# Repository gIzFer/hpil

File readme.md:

# HP-IL bridge/translator to USB/Serial

## What does it do
So what does this do? The device simply takes what it receives from the HP-IL side and sends it over serial. Same in the other direction. sends 2 bytes, the `command` and the `data` terminated with a `'\n'` (ascii 10) character

## Why
I had a 3468A and wanted to control it from my computer and make the electronics circuit simple an easy and of parts everyone could have at hand. Difficulty was relayed onto the firmware, but even so was kept simple without implementing the state machines of the protocol.

## Materials needed
- Atmega328p
- 2 NPN and 4 PNP transistors. 2 PNP handle the input and the other 2 and 2 are for a push pull arrangement to send data. I sprinkled on them some diodes to speed them up.
- Ethernet transformer. Fastest pulses are around 1µs and an ethernet transformer seems to be able to handle that quite well. You can find them in every device having a rj45 port, old computers, routers, switches, etc.

[client docs](./client/readme.md)

## Added made up codes

### 1XX

They are for extra messages you can send to the device, like asking it to just send the message it just received

#### 1XX List of codes
- 101: send back the last message received
- 102: get calibration data of the HP3468 dmm
- 103: get firmware version
- 104: set calibration value of the HP3468 dmm. Has 5 parameters: first one is the range setting to set. Since there are 12 ranges and two values per range the even values are offsets and odd values are gains. i.e.: `104 6 0 0 0 0` set the offset of the fourth range to 0.i.e.: `104 1 0 0 0 0` set the gain of the first range to 0.
- 105: print processed calibration values of the HP3468 dmm
- 106: print a quick read of the HP3468 dmm

### 2XX

They are for extra messages you can receive from the device  like errors

#### 2XX List of codes
- 201: received message buffer overflowed, answers with 201 and the last byte it received
- 202: in command 104, trying to set a cal value the value was more than 23; there are only 12 ranges with 2 values per range (offset and gain), 0 to 23.

# todo:
- read pins instead of delays (NOPs) when talking to be able to read answer at the same time im writing
- add images to readme
- add "console mode" so no need for the python client, to be able to directly send the commands to it
- send and write calibration data

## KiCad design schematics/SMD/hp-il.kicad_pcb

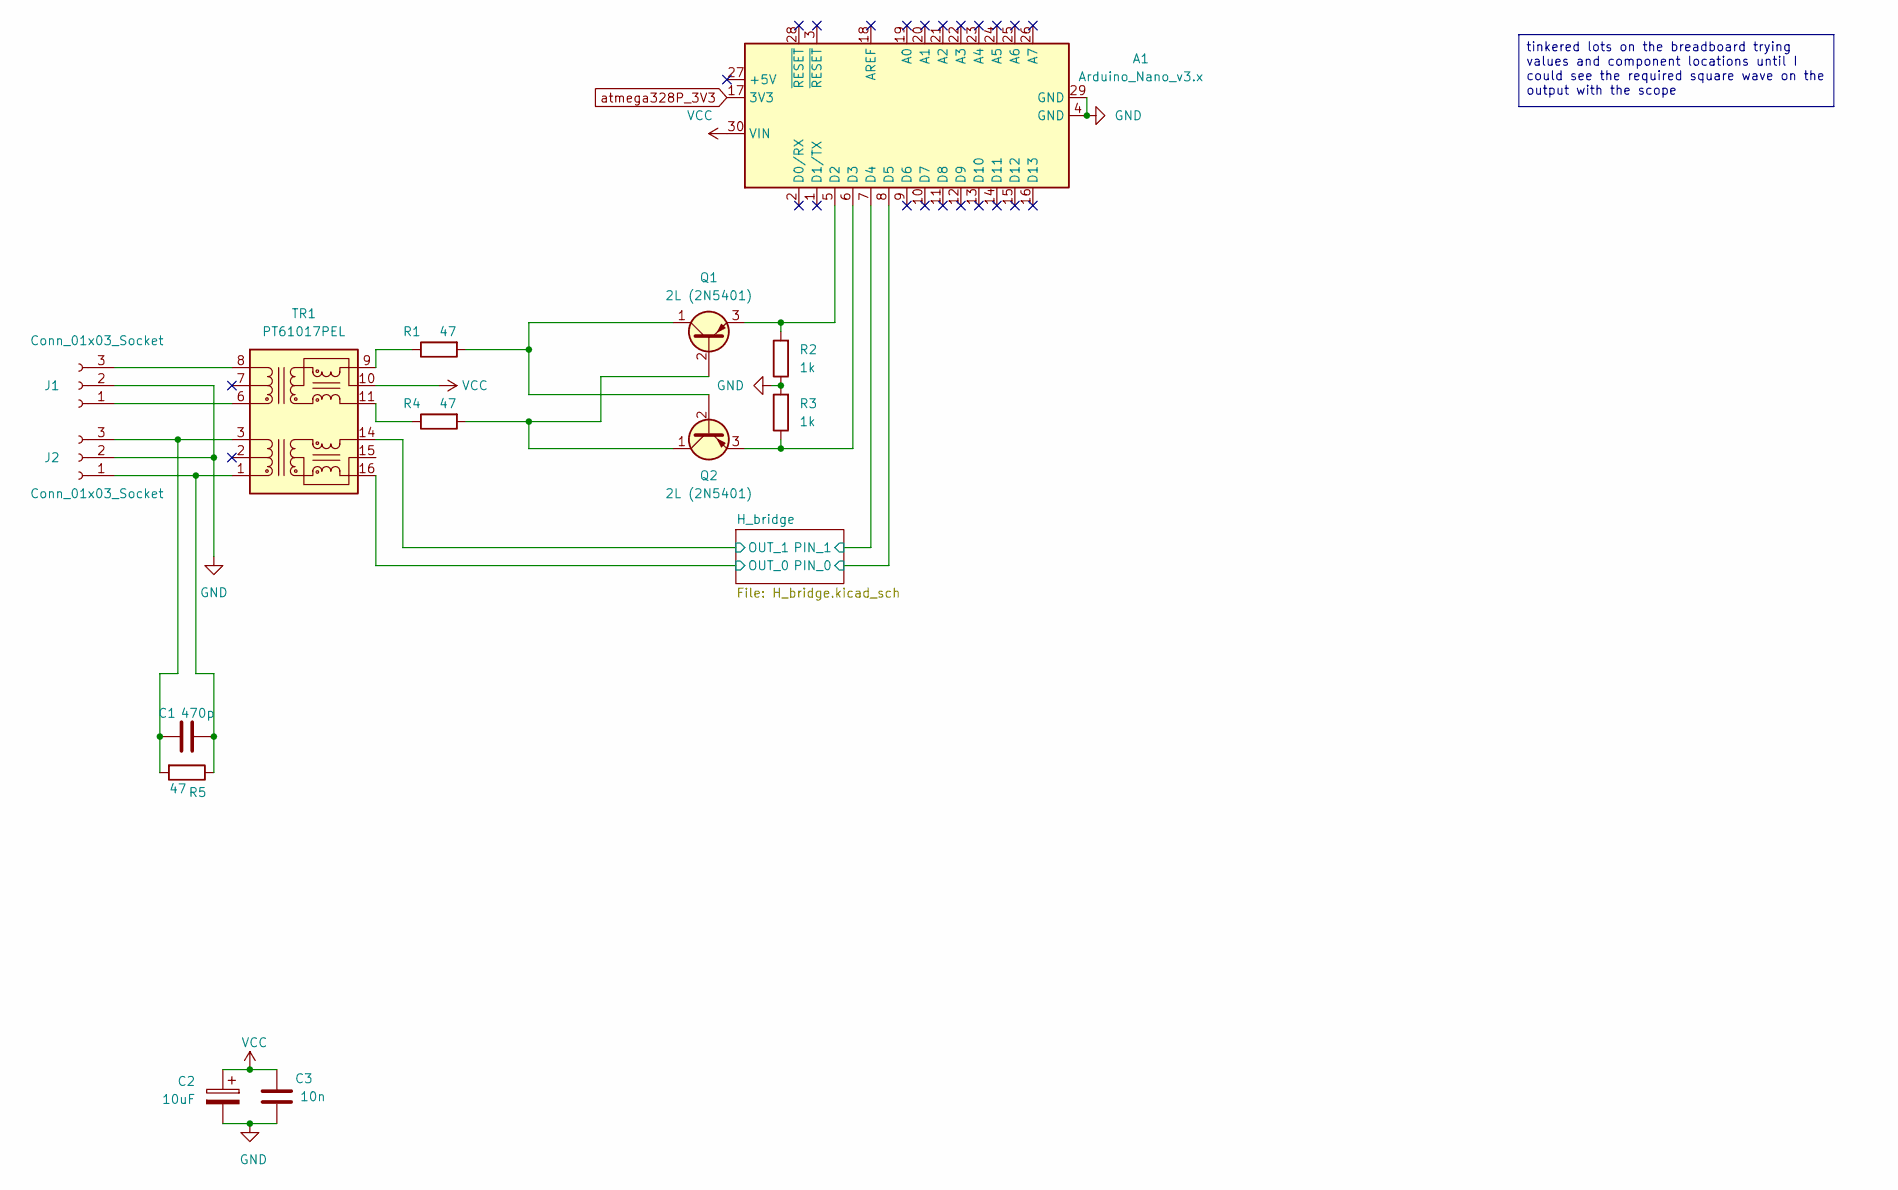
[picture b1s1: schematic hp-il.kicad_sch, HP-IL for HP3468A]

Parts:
A1: Arduino_Nano_v3.x; Arduino_Nano
C1: 470p; C_0603_1608Metric_Pad1.08x0.95mm_HandSolder
C2: 10uF; CP_Radial_D4.0mm_P2.00mm
C3: 10n; C_0603_1608Metric_Pad1.08x0.95mm_HandSolder
J1, J2: Conn_01x03_Socket; PinHeader_1x03_P2.54mm_Vertical
Q1, Q2: 2L (2N5401); SOT-23_Handsoldering_(5401_2L)
R1, R4, R5: 47; R_0603_1608Metric_Pad0.98x0.95mm_HandSolder
R2, R3: 1k; R_0603_1608Metric_Pad0.98x0.95mm_HandSolder
TR1: PT61017PEL; Transformer_Ethernet_Bourns_PT61017PEL

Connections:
/H_bridge/OUT_0: TR1.16 (TX+); also elsewhere on the board
/H_bridge/OUT_1: TR1.14 (TX-); also elsewhere on the board
/H_bridge/PIN_0: A1.8 (D5); also elsewhere on the board
/H_bridge/PIN_1: A1.7 (D4); also elsewhere on the board
GND: A1.4 (GND), A1.29 (GND), C2.2, C3.2, J1.2, J2.2, R2.1, R3.2; also elsewhere on the board
unnamed: A1.5 (D2), Q1.3 (E), R2.2
unnamed: A1.6 (D3), Q2.3 (E), R3.1
unnamed: J1.1, TR1.6 (RD+)
unnamed: J1.3, TR1.8 (RD-)
unnamed: C1.2, J2.1, R5.1, TR1.1 (TD+)
unnamed: C1.1, J2.3, R5.2, TR1.3 (TD-)
unnamed: Q1.2 (B), Q2.1 (C), R4.2
unnamed: Q1.1 (C), Q2.2 (B), R1.2
unnamed: R4.1, TR1.11 (RX+)
unnamed: R1.1, TR1.9 (RX-)
VCC: A1.30 (VIN), C2.1, C3.1, TR1.10 (C_RX)
atmega328P_3V3: A1.17 (3V3); also elsewhere on the board

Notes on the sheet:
tinkered lots on the breadboard trying values and component locations until I could see the required square wave on the output with the scope

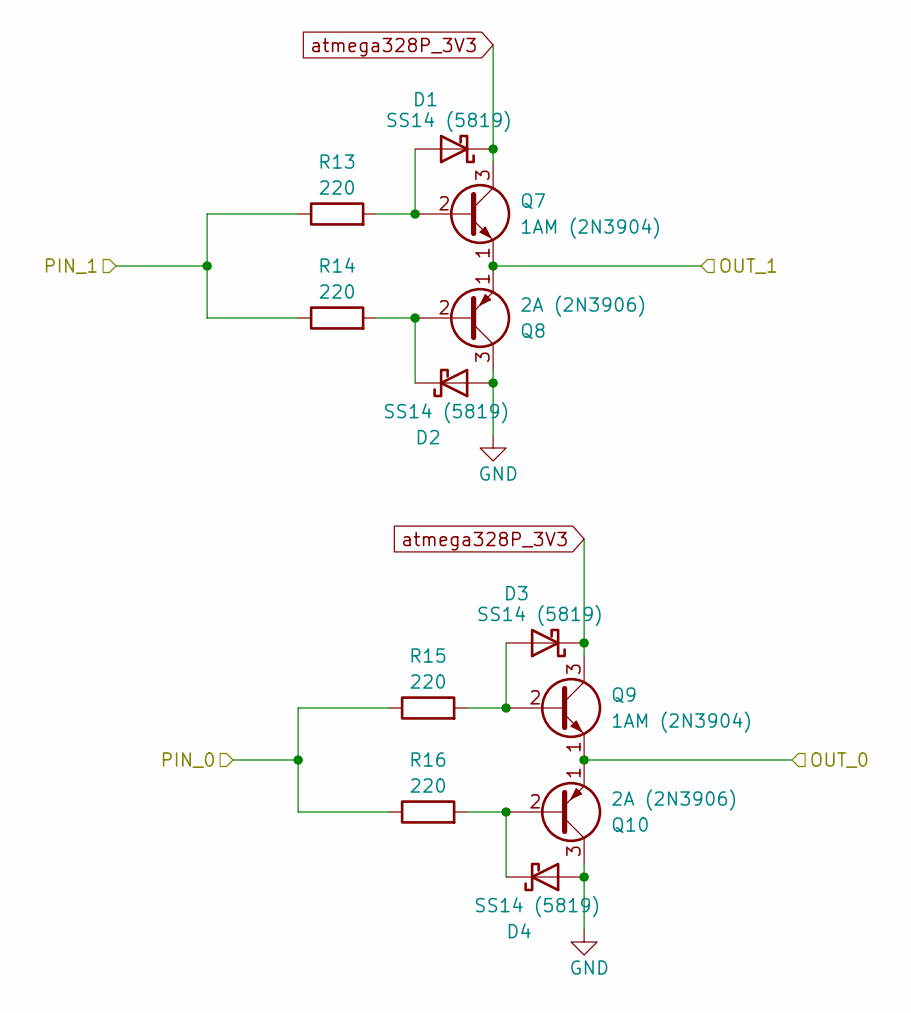
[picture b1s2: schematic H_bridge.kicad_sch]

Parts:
D1, D2, D3, D4: SS14 (5819); D_SMA_Handsoldering
Q7, Q9: 1AM (2N3904); SOT-23_Handsoldering_(3904_1AM)(3906_2A)
Q8, Q10: 2A (2N3906); SOT-23_Handsoldering_(3904_1AM)(3906_2A)
R13, R14, R15, R16: 220; R_0603_1608Metric_Pad0.98x0.95mm_HandSolder

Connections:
/H_bridge/OUT_0: Q9.1 (E), Q10.1 (E); also elsewhere on the board
/H_bridge/OUT_1: Q7.1 (E), Q8.1 (E); also elsewhere on the board
/H_bridge/PIN_0: R15.1, R16.1; also elsewhere on the board
/H_bridge/PIN_1: R13.1, R14.1; also elsewhere on the board
GND: D2.2 (A), D4.2 (A), Q8.3 (C), Q10.3 (C); also elsewhere on the board
unnamed: D1.2 (A), Q7.2 (B), R13.2
unnamed: D2.1 (K), Q8.2 (B), R14.2
unnamed: D3.2 (A), Q9.2 (B), R15.2
unnamed: D4.1 (K), Q10.2 (B), R16.2
atmega328P_3V3: D1.1 (K), D3.1 (K), Q7.3 (C), Q9.3 (C); also elsewhere on the board

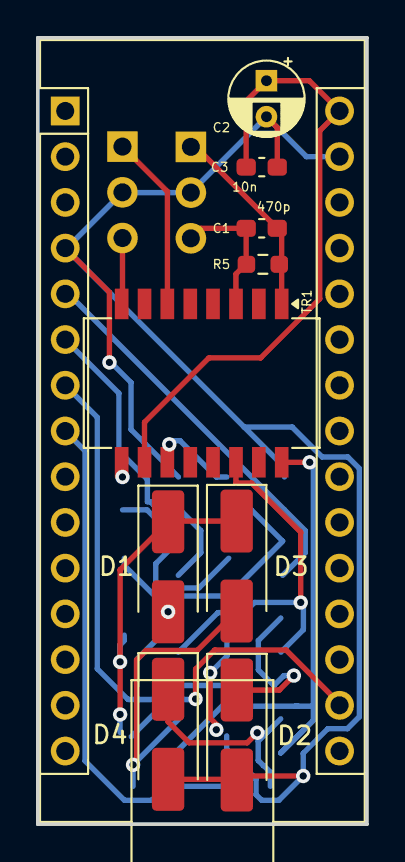
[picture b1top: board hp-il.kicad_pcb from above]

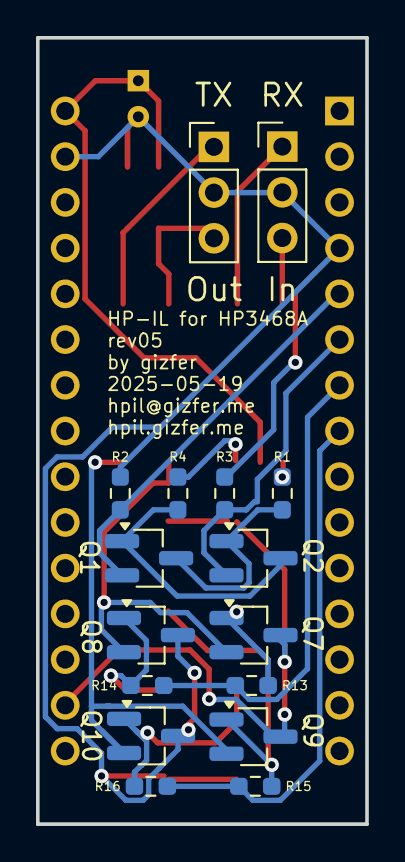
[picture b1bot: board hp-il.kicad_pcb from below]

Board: 2 copper layers, 18.3 x 43.7 mm, 26 parts (16 on the bottom side), 21 nets.

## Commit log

2023-11-02 optimized, it can now keep up
2023-11-02 split into files for organization
2023-11-08 can now send pulses through
2024-02-06 Can receive and talk
2024-02-07 kinda rebase
2024-02-08 kinda rebase 2
2024-02-08 it works
2024-02-08 it works 2
2024-03-07 added hpil class for control
2024-03-09 workssss
2024-03-09 added messages
2024-03-09 working and cleaned
2024-03-09 optimized and cleaned
2024-12-01 works :DDD
2024-12-02 minor rework, added comments
2024-12-02 added schematic and client
2024-12-02 renamed schematic folder and cleaned files
2024-12-02 added .gitignore to schematics
2024-12-02 added and organized .gitignores
2024-12-02 firmware code cleanup
2024-12-02 worked on docs
2024-12-02 added to the todo list
2024-12-02 Create LICENSE
    added a license
2025-06-15 bugfixes on the signal decoding
2025-06-16 added retry system with talk and rawTalk
2025-06-16 added getCal method
2025-06-16 added "console mode" to the todo list
2025-06-16 added GetCal "docs"
2025-06-16 created compact SMD version, kept THT one
2025-06-16 removed upload.sh, using make
2025-06-20 added get cal data code 102
2025-06-20 added boot str to detect when ready
2025-06-20 added firmware version
2025-06-20 updated client with new features
2025-06-28 added code to decode and encode gain value
2025-06-28 specified detail on custom code
2025-06-28 added calculation of parity
2025-06-29 bugfixes and now can generate cal string with checksum
2025-06-29 code cleanup and cal print command
2025-06-29 added comments
2025-06-29 removed unused debug defines
2025-06-29 added quick read command for HP3468A
